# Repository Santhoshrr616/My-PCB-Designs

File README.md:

# My-PCB-Designs
A collection of my PCB design projects, electronic circuits and hardware development work using KiCad.

# My PCB Designs

Welcome to my PCB Design Repository!

This repository contains my electronics hardware design projects developed using KiCad.

## About

I am an Electrical and Electronics Engineering student interested in PCB design, embedded systems, electronics hardware development and circuit design.

## Software & Tools

* KiCad 7
* Electronic circuit design
* PCB layout and routing
* Gerber generation
* Hardware testing

## Projects

| No. | Project                    | Status      |
| --- | -------------------------- | ----------- |
| 01  | Stop Light Controller PCB  | In Progress |
| 02  | 12V to 5V Buck Converter   | Planned     |
| 03  | Water Level Controller PCB | Planned     |

## What You Will Find

* Circuit schematics
* PCB layouts
* Component details and BOM
* 3D PCB views
* Gerber manufacturing files
* Testing and documentation

## Objective

To develop practical electronics hardware design skills through real-world PCB projects and continuous learning.

More projects will be added as I continue developing my hardware design skills.

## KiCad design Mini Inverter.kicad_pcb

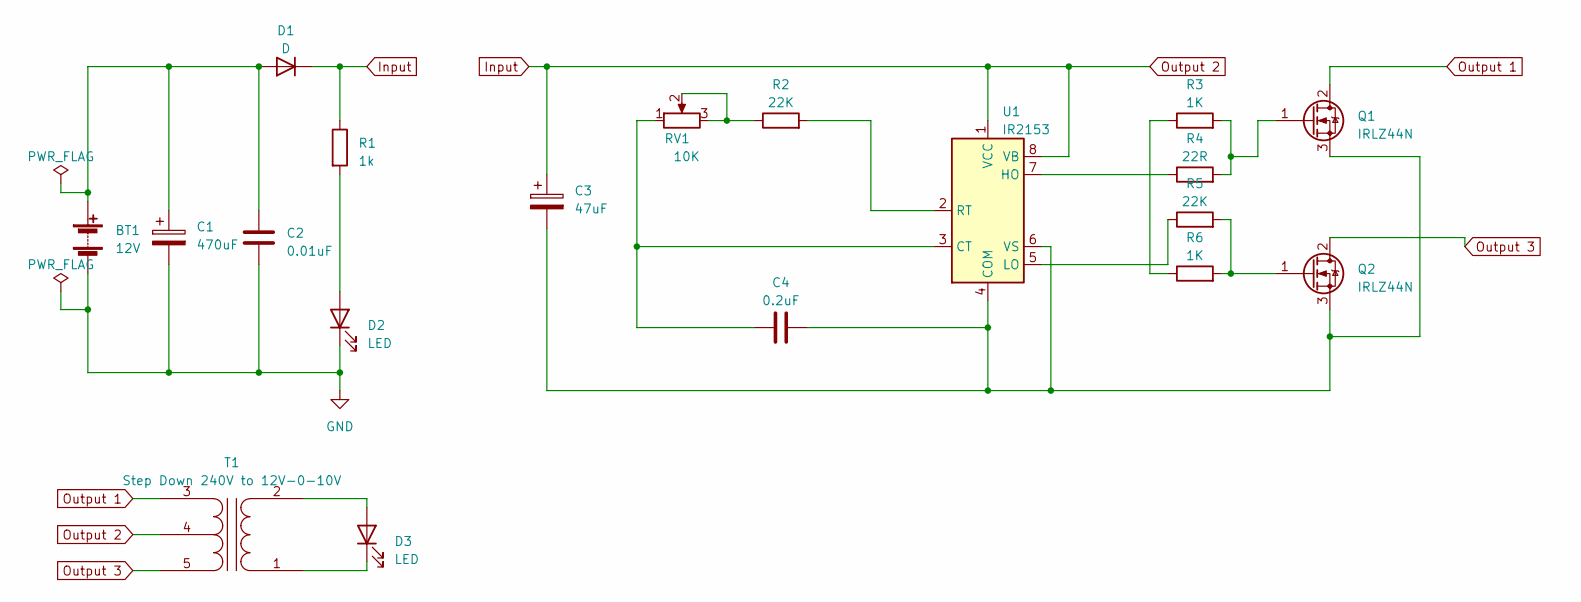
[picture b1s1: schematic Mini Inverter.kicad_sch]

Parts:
BT1: 12V; TerminalBlock_TE_282834-2_1x02_P2.54mm_Horizontal
C1: 470uF; CP_Radial_D6.3mm_P2.50mm
C2: 0.01uF; C_Disc_D3.0mm_W1.6mm_P2.50mm
C3: 47uF; CP_Radial_D6.3mm_P2.50mm
C4: 0.2uF; C_Disc_D3.0mm_W1.6mm_P2.50mm
D1: D; D_DO-41_SOD81_P10.16mm_Horizontal
D2: LED; TerminalBlock_TE_282834-2_1x02_P2.54mm_Horizontal
D3: LED; LED_D5.0mm
Q1, Q2: IRLZ44N; TO-220-3_Vertical
R1: 1k; R_Axial_DIN0204_L3.6mm_D1.6mm_P5.08mm_Horizontal
R2, R5: 22K; R_Axial_DIN0204_L3.6mm_D1.6mm_P5.08mm_Horizontal
R3, R6: 1K; R_Axial_DIN0204_L3.6mm_D1.6mm_P5.08mm_Horizontal
R4: 22R; R_Axial_DIN0204_L3.6mm_D1.6mm_P5.08mm_Horizontal
RV1: 10K; Potentiometer_ACP_CA6-H2,5_Horizontal
T1: Step Down 240V to 12V-0-10V; TerminalBlock_TE_282834-5_1x05_P2.54mm_Horizontal
U1: IR2153; DIP-8_W7.62mm

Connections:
GND: BT1.2 (-), C1.2, C2.2, D2.1 (K)
Input: C3.1, D1.1 (K), R1.1, T1.4 (SC), U1.1 (VCC), U1.8 (VB)
unnamed: BT1.1 (+), C1.1, C2.1, D1.2 (A)
unnamed: D2.2 (A), R1.2
unnamed: D3.2 (A), T1.2 (AB)
unnamed: D3.1 (K), T1.1 (AA)
unnamed: Q1.1 (G), R3.2, R4.2
unnamed: C3.2, C4.2, Q1.3 (S), Q2.3 (S), U1.4 (COM), U1.6 (VS)
unnamed: Q2.1 (G), R5.2, R6.2
unnamed: R2.1, RV1.2, RV1.3
unnamed: R3.1, R6.1
unnamed: C4.1, RV1.1, U1.3 (CT)
unnamed: R4.1, U1.7 (HO)
unnamed: R5.1, U1.5 (LO)
unnamed: R2.2, U1.2 (RT)
Output 1: Q1.2 (D), T1.3 (SA)
Output 3: Q2.2 (D), T1.5 (SB)

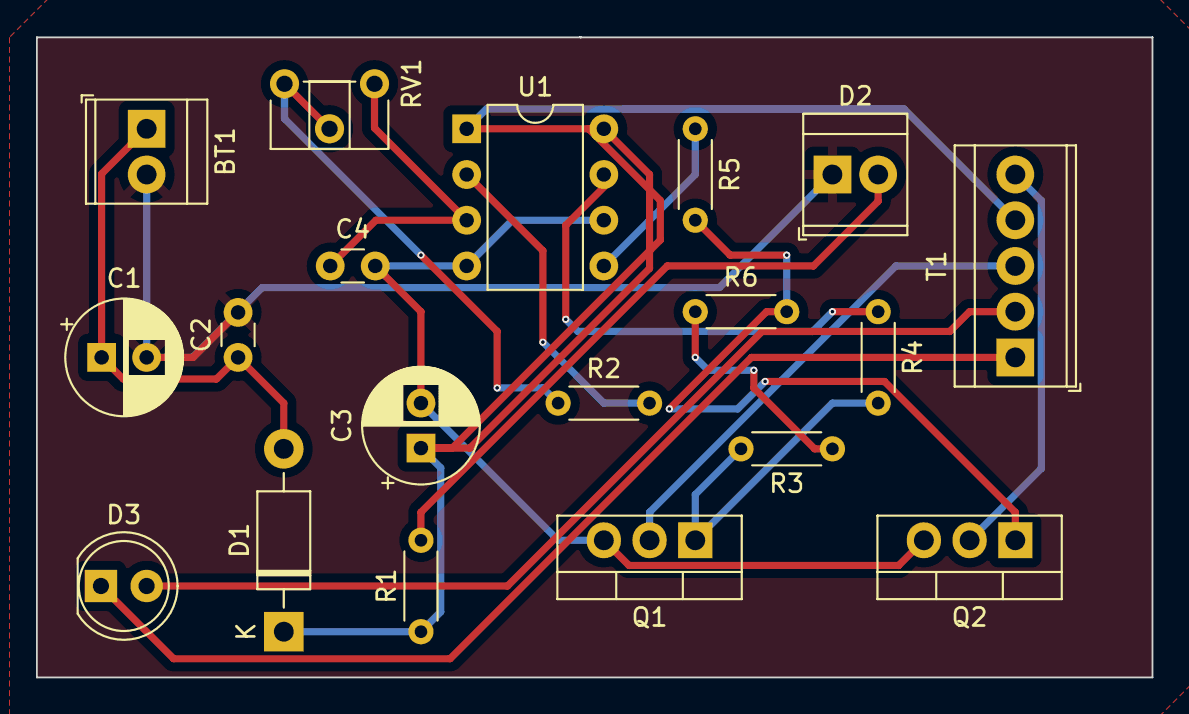
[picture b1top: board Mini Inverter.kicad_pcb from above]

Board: 2 copper layers, 62.0 x 35.6 mm, 19 parts (0 on the bottom side), 17 nets.

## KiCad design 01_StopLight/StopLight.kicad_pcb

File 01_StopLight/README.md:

# Stop Light Controller PCB

## Project Overview
PCB design of a Stop Light Controller.

## Software Used
- KiCad 7

## Project Files
- Schematic
- PCB Layout
- 3D PCB View
- Gerber Files

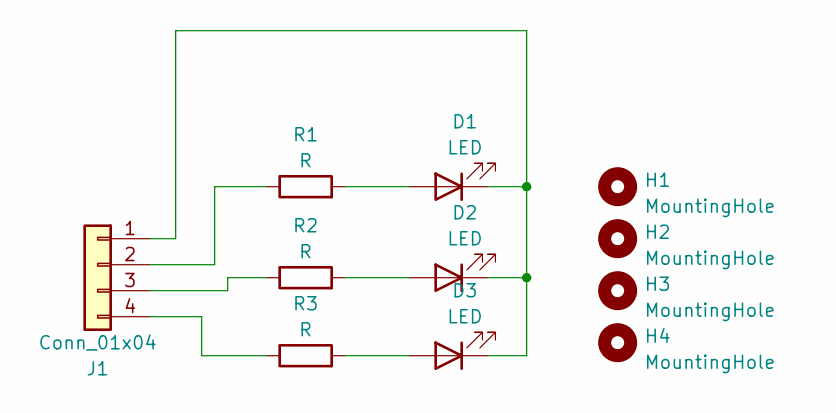
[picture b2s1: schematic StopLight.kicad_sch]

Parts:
D1, D2, D3: LED; LED_D3.0mm
H1, H2, H3, H4: MountingHole; MountingHole_2.5mm_Pad
J1: Conn_01x04; PinHeader_1x04_P2.54mm_Horizontal
R1, R2, R3: R; R_Axial_DIN0204_L3.6mm_D1.6mm_P5.08mm_Horizontal

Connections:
unnamed: D1.2 (A), R1.2
unnamed: D1.1 (K), D2.1 (K), D3.1 (K), J1.1
unnamed: D2.2 (A), R2.2
unnamed: D3.2 (A), R3.2
unnamed: J1.2, R1.1
unnamed: J1.3, R2.1
unnamed: J1.4, R3.1

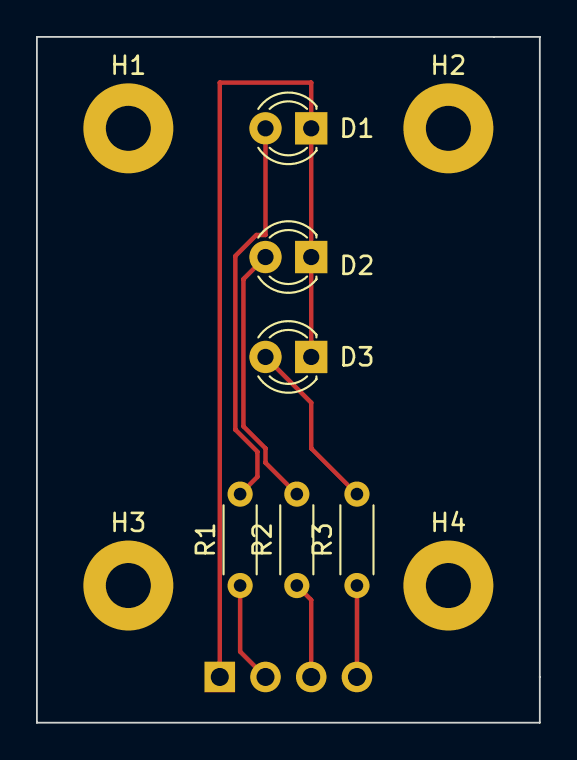
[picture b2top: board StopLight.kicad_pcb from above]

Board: 2 copper layers, 27.9 x 38.1 mm, 11 parts (1 on the bottom side), 7 nets.
